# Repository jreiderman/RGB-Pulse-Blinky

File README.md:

# RGB-Pulse-Blinky
This project measures a person's pulse on their finger tip and blinks an RGB LED accordingly.
 Project is on hold until I decide to spend time to figure out the amplification stage.

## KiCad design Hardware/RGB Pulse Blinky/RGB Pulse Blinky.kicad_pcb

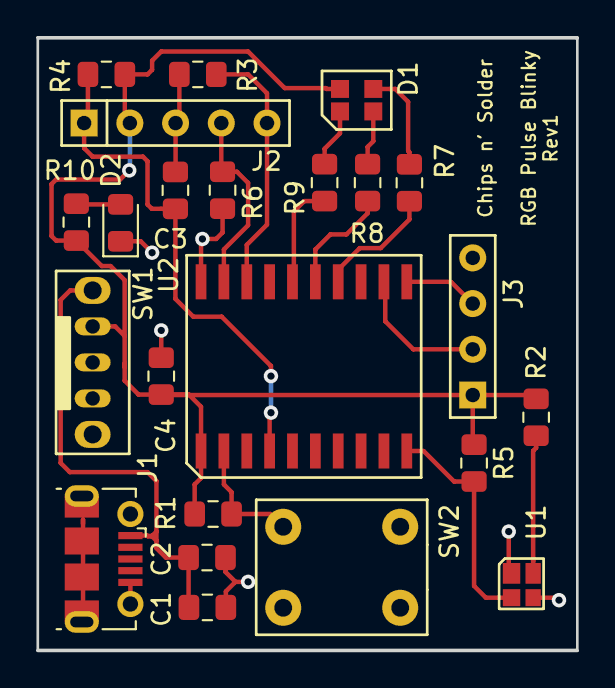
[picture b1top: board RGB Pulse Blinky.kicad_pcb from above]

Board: 2 copper layers, 30.0 x 34.0 mm, 23 parts (0 on the bottom side), 18 nets.

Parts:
C1: 10u; C_0805_2012Metric_Pad1.15x1.40mm_HandSolder
C2: 1u; C_0805_2012Metric_Pad1.15x1.40mm_HandSolder
C3, C4: 0.1uF; C_0805_2012Metric_Pad1.15x1.40mm_HandSolder
D1: LED_RGB_Common_Anode; LED_RGB
D2: LED; LED_0805_2012Metric_Pad1.15x1.40mm_HandSolder
J1: USB_B_Micro; USB_Micro-B_Molex-105017-0001
J2: Header_Male_5_Pin
J3: Header_Male_4_Pin
R1, R3, R4, R5, R6: 10k; R_0805_2012Metric_Pad1.15x1.40mm_HandSolder
R2: 220; R_0805_2012Metric_Pad1.15x1.40mm_HandSolder
R7, R10: 150; R_0805_2012Metric_Pad1.15x1.40mm_HandSolder
R8, R9: 100; R_0805_2012Metric_Pad1.15x1.40mm_HandSolder
SW1: SW_SPST; Switch_Slider
SW2: SW_Push; Switch_Push_Button
U1: VCNT2020
U2: PIC16F1574; PIC16F1574(SOIC-20)

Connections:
GND: C1.2, C2.2, C3.2, C4.2, D2.1, J1.5, J1.6, J2.3, J3.4, R3.2, R6.2, SW2.1, U1.1, U1.4, U2.20
unnamed: C1.1, C2.1, J1.1, SW1.1
unnamed: C3.1, J2.1, R4.2, U2.4
unnamed: D1.1, R7.2
unnamed: D1.2, R8.2
unnamed: D1.3, R9.2
unnamed: D2.2, R10.2
unnamed: J2.4, R6.1, U2.19
unnamed: J2.5, R3.1, U2.18
unnamed: J3.2, U2.12
unnamed: J3.3, U2.11
unnamed: R1.2, SW2.2, U2.2
unnamed: R2.2, U1.3
unnamed: R5.2, U1.2, U2.10
unnamed: R7.1, U2.14
unnamed: R8.1, U2.15
unnamed: R9.1, U2.16
VDD: C4.1, D1.4, J2.2, J3.1, R1.1, R2.1, R4.1, R5.1, R10.1, SW1.2, U2.1

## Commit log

2018-08-11 Added project competition information to README.
2018-08-15 Initial schematic complete.
2018-08-22 Updated power circuit. Added component footprints.
2018-08-25 Added more part footprints. Completed PCB layout. Generated gerbers.
2019-03-30 Update README to show project is currently inactive.
2019-03-30 Update README.md
    Corrected typo.
